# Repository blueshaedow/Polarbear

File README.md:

# Polarbear
Repo for custom mechanical keyboard
test

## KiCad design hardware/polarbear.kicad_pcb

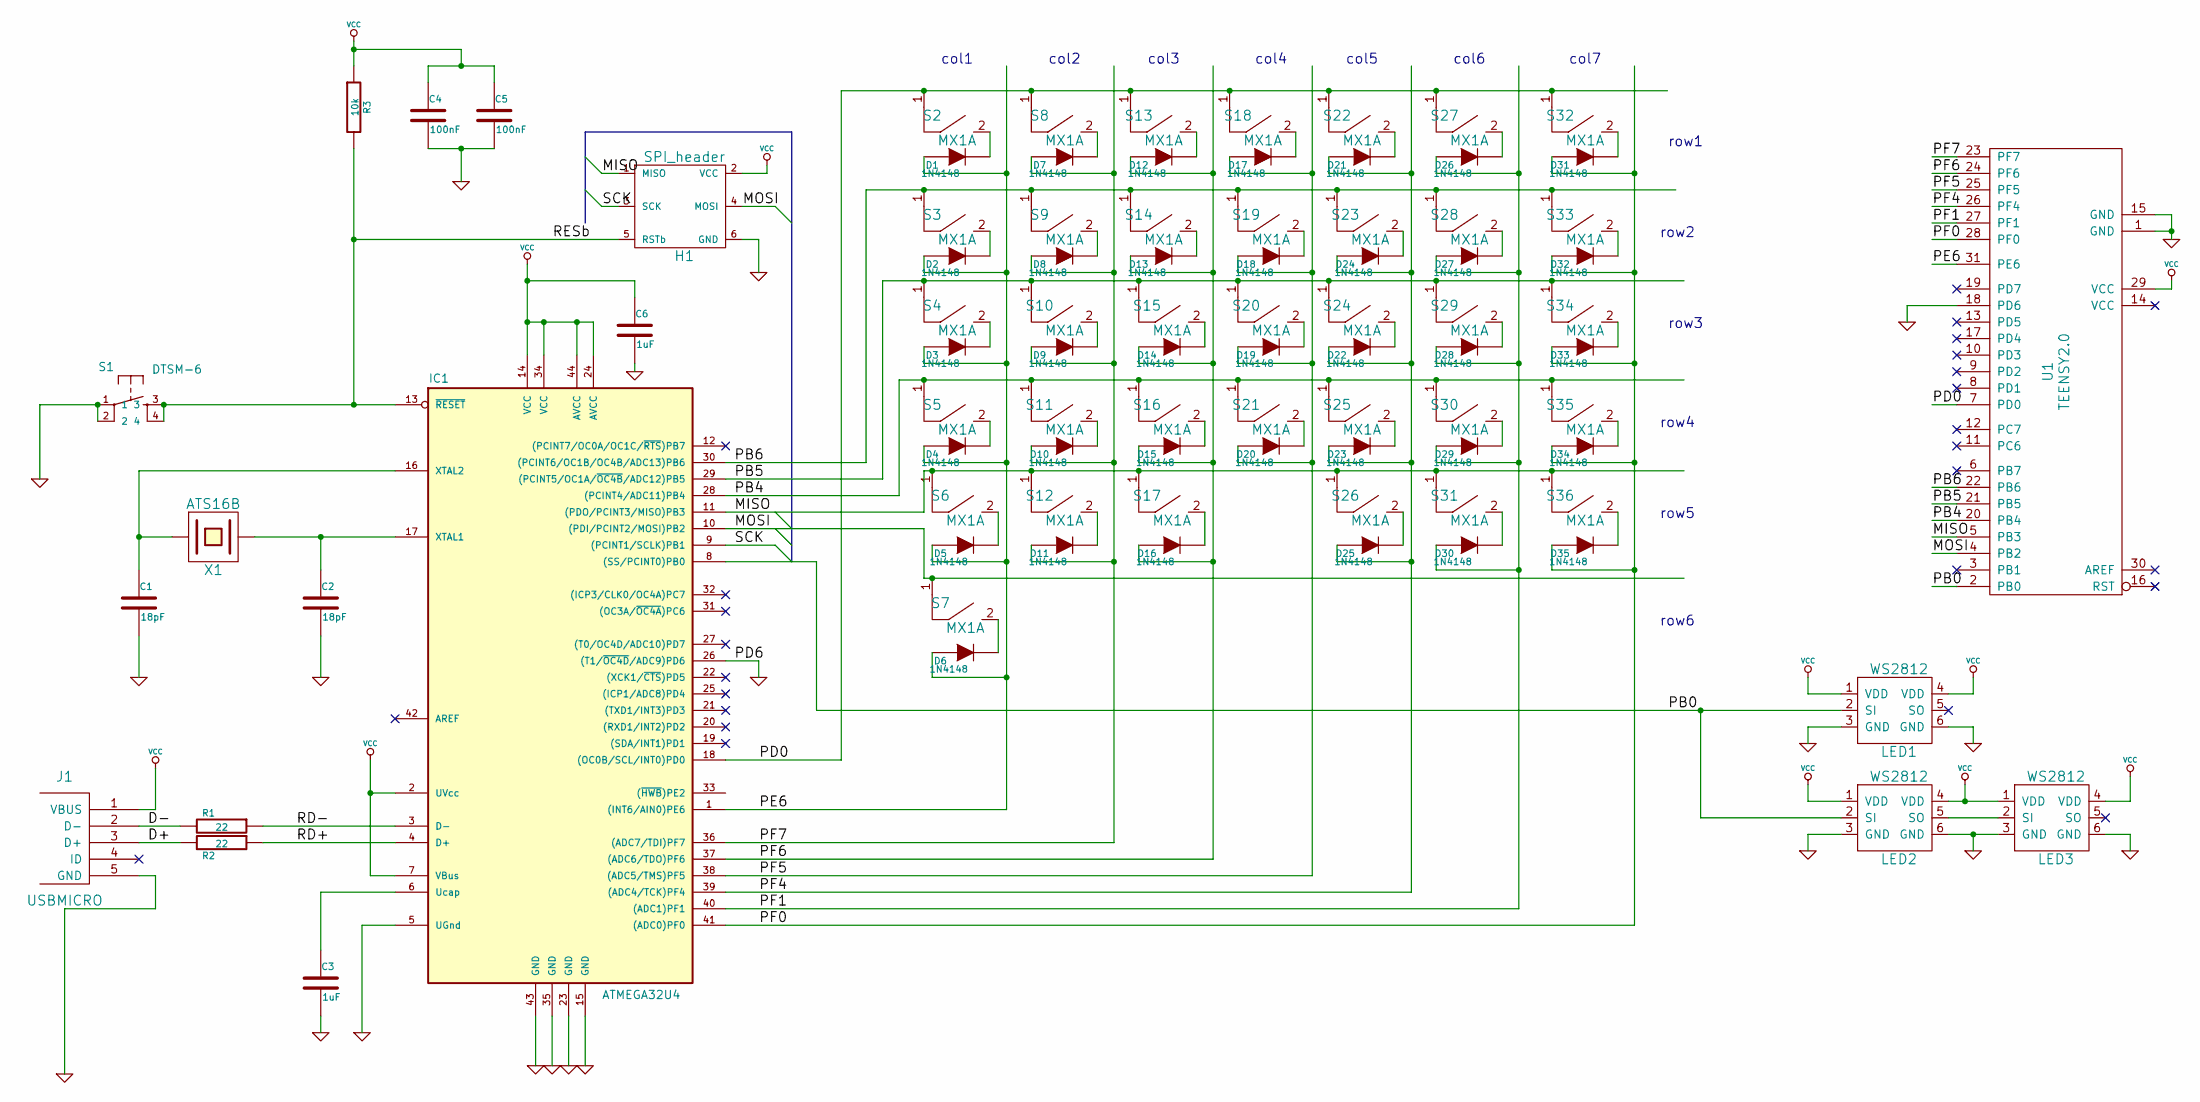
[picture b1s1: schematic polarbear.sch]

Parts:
C1, C2: 18pF; SM0805
C3, C6: 1uF; SM0805
C4, C5: 100nF; SM0805
D1, D2, D3, D4, D5, D6, D7, D8, D9, D10, D11, D12, D13, D14, D15, D16, D17, D18, D19, D20, D21, D22, D23, D24, D25, D26, D27, D28, D29, D30, D31, D32, D33, D34, D35: 1N4148; 1N4148_SOD123
H1: SPI_header
IC1: ATMEGA32U4; TQFP44
J1: USBMICRO; conn_usbmicro
LED1, LED2, LED3: WS2812; WS2128
R1, R2: 22; SM0805
R3: 10k; SM0805
S1: DTSM-6; KSEM31GLFS
S2, S3, S4, S5, S6, S7, S8, S9, S10, S11, S12, S13, S14, S15, S16, S17, S18, S19, S20, S21, S22, S23, S24, S25, S26, S27, S28, S29, S30, S31, S32, S33, S34, S35, S36: MX1A; MX1A_ddouble_sided
U1: TEENSY2.0; TEENSY_2.0
X1: ATS16B

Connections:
/D+: J1.3 (D+), R2.2
/D-: J1.2 (D-), R1.2
/MISO: H1.1 (MISO), IC1.11 ((PDO/PCINT3/MISO)PB3), S6.1, S12.1, S17.1, S26.1, S31.1, S36.1, U1.5 (PB3)
/MOSI: H1.4 (MOSI), IC1.10 ((PDI/PCINT2/MOSI)PB2), S7.1, U1.4 (PB2)
/PB0: IC1.8 ((SS/PCINT0)PB0), LED1.2 (SI), LED2.2 (SI), U1.2 (PB0)
/PB4: IC1.28 ((PCINT4/ADC11)PB4), S5.1, S11.1, S16.1, S21.1, S25.1, S30.1, S35.1, U1.20 (PB4)
/PB5: IC1.29 ((PCINT5/OC1A/~OC4B~/ADC12)PB5), S4.1, S10.1, S15.1, S20.1, S24.1, S29.1, S34.1, U1.21 (PB5)
/PB6: IC1.30 ((PCINT6/OC1B/OC4B/ADC13)PB6), S3.1, S9.1, S14.1, S19.1, S23.1, S28.1, S33.1, U1.22 (PB6)
/PD0: IC1.18 ((OC0B/SCL/INT0)PD0), S2.1, S8.1, S13.1, S18.1, S22.1, S27.1, S32.1, U1.7 (PD0)
/PE6: D1.1 (A), D2.1 (A), D3.1 (A), D4.1 (A), D5.1 (A), D6.1 (A), IC1.1 ((INT6/AIN0)PE6), U1.31 (PE6)
/PF0: D31.1 (A), D32.1 (A), D33.1 (A), D34.1 (A), D35.1 (A), IC1.41 ((ADC0)PF0), U1.28 (PF0)
/PF1: D26.1 (A), D27.1 (A), D28.1 (A), D29.1 (A), D30.1 (A), IC1.40 ((ADC1)PF1), U1.27 (PF1)
/PF4: D21.1 (A), D22.1 (A), D23.1 (A), D24.1 (A), D25.1 (A), IC1.39 ((ADC4/TCK)PF4), U1.26 (PF4)
/PF5: D17.1 (A), D18.1 (A), D19.1 (A), D20.1 (A), IC1.38 ((ADC5/TMS)PF5), U1.25 (PF5)
/PF6: D12.1 (A), D13.1 (A), D14.1 (A), D15.1 (A), D16.1 (A), IC1.37 ((ADC6/TDO)PF6), U1.24 (PF6)
/PF7: D7.1 (A), D8.1 (A), D9.1 (A), D10.1 (A), D11.1 (A), IC1.36 ((ADC7/TDI)PF7), U1.23 (PF7)
/RD+: IC1.4 (D+), R2.1
/RD-: IC1.3 (D-), R1.1
/RESb: H1.5 (RSTb), IC1.13 (~RESET~), R3.2, S1.3, S1.4; also elsewhere on the board
/SCK: H1.3 (SCK), IC1.9 ((PCINT1/SCLK)PB1)
GND: C1.2, C2.2, C3.2, C4.2, C5.2, C6.2, H1.6 (GND), IC1.5 (UGnd), IC1.15 (GND), IC1.23 (GND), IC1.26 ((T1/~OC4D~/ADC9)PD6), IC1.35 (GND), IC1.43 (GND), J1.5 (GND), LED1.3 (GND), LED1.6 (GND), LED2.3 (GND), LED2.6 (GND), LED3.3 (GND), LED3.6 (GND), S1.1, S1.2, U1.1 (GND), U1.15 (GND), U1.18 (PD6); also elsewhere on the board
unnamed: C1.1, IC1.16 (XTAL2), X1.1
unnamed: C2.1, IC1.17 (XTAL1), X1.2
unnamed: C3.1, IC1.6 (Ucap)
unnamed: D1.2 (K), S2.2
unnamed: D2.2 (K), S3.2
unnamed: D3.2 (K), S4.2
unnamed: D4.2 (K), S5.2
unnamed: D5.2 (K), S6.2
unnamed: D6.2 (K), S7.2
unnamed: D7.2 (K), S8.2
unnamed: D8.2 (K), S9.2
unnamed: D9.2 (K), S10.2
unnamed: D10.2 (K), S11.2
unnamed: D11.2 (K), S12.2
unnamed: D12.2 (K), S13.2
unnamed: D13.2 (K), S14.2
unnamed: D14.2 (K), S15.2
unnamed: D15.2 (K), S16.2
unnamed: D16.2 (K), S17.2
unnamed: D17.2 (K), S18.2
unnamed: D18.2 (K), S19.2
unnamed: D19.2 (K), S20.2
unnamed: D20.2 (K), S21.2
unnamed: D21.2 (K), S22.2
unnamed: D22.2 (K), S24.2
unnamed: D23.2 (K), S25.2
unnamed: D24.2 (K), S23.2
unnamed: D25.2 (K), S26.2
unnamed: D26.2 (K), S27.2
unnamed: D27.2 (K), S28.2
unnamed: D28.2 (K), S29.2
unnamed: D29.2 (K), S30.2
unnamed: D30.2 (K), S31.2
unnamed: D31.2 (K), S32.2
unnamed: D32.2 (K), S33.2
unnamed: D33.2 (K), S34.2
unnamed: D34.2 (K), S35.2
unnamed: D35.2 (K), S36.2
unnamed: LED2.5 (SO), LED3.2 (SI)
VCC: C4.1, C5.1, C6.1, H1.2 (VCC), IC1.2 (UVcc), IC1.7 (VBus), IC1.14 (VCC), IC1.24 (AVCC), IC1.34 (VCC), IC1.44 (AVCC), J1.1 (VBUS), LED1.1 (VDD), LED1.4 (VDD), LED2.1 (VDD), LED2.4 (VDD), LED3.1 (VDD), LED3.4 (VDD), R3.1, U1.29 (VCC)

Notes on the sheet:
col1
col2
col3
col4
col5
col6
col7
row1
row2
row3
row4
row5
row6

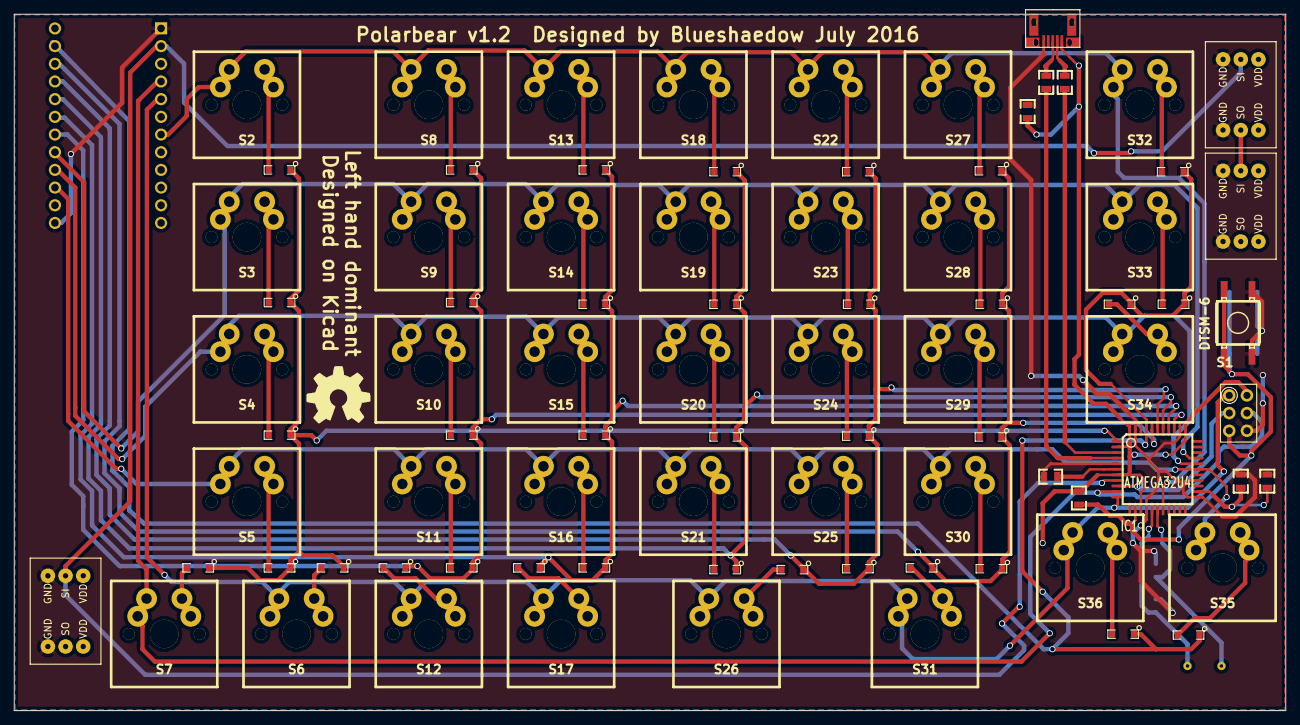
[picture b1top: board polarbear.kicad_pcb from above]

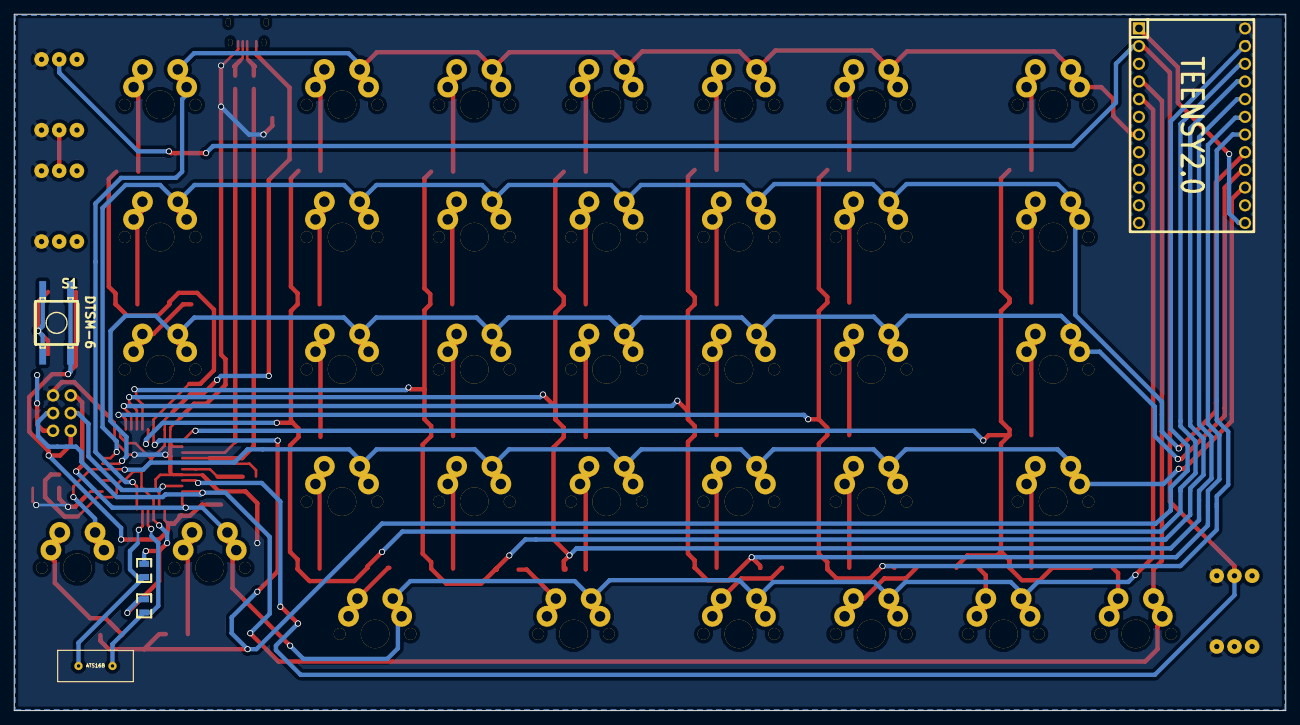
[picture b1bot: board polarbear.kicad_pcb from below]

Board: 2 copper layers, 182.6 x 100.0 mm, 90 parts (5 on the bottom side), 61 nets.

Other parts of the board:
S1#2: DTSM-6; KSEM31GLFS
open_hardware_logo: open_hardware_logo

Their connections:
/RESb: S1#2.3, S1#2.4; also elsewhere on the board
GND: S1#2.1, S1#2.2; also elsewhere on the board

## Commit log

2016-02-22 Checking in TMK firmware
2016-02-23 Remove polarbear_tester
2016-02-23 Adding polarbear directory
2016-02-23 Adding build folder
2016-05-28 Checking in Kicad board files
2016-05-28 Removing .dep folder
2016-05-28 Adding enclosure CAD drawings
2016-06-27 Adding support for Tennsy 2.0
2016-07-08 Update with WS2128 module
2016-07-08 Adding WS2128 LED module
2016-07-08 Test
2016-07-08 Revert "Test"
    This reverts commit 3ecfec94606e7dc01cccefd219bfc1d68255ce28.
2016-07-08 Revert "Revert "Test""
    This reverts commit 2296453375fb4d6b4d08c1c07fde1918d5807adc.
2016-07-10 Adding name to WS2128 pin
2016-07-10 Removing old generated gerber
2016-07-10 Modified design to include 3 WS2128 LED module, added open hardware logo, and re-did routing for VDD/GND.
